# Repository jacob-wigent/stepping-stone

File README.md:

---

> 🚧 Under development

Stepping Stone is a 4-axis stepper motor control platform designed for robotics and CNC development. With hardware built around an STM32G4 MCU and TMC2209 drivers, it supports coordinated multi-axis motion, encoder feedback, stall-sense homing, and CAN/USB connectivity for flexible development and testing. The desktop application connects to the hardware to provide detailed, real-time telemetry and visualization support.

Designed as a “stepping stone” in motion-control prototyping, it bridges the gap between simple stepper driver breakouts and full CNC or robotics systems, providing a reusable platform for early development.

### Navigate

| |  |  |
|-----------|---------|---------|
| **[Hardware](./hardware)** | Circuit design and PCB layout | KiCad design files, simulations |
| **[Firmware](./firmware)** | Microcontroller implementation | STM32 code, CubeMX configuration |
| **[Software](./software)** | Desktop telemetry bridge | GUI application code |

## Planned Features

- **Power Input**: 5-24V input from bench supply or dedicated PSU.
- **Motors**: 4 independent stepper motor channels.
- **Encoders**: 4 quadrature encoder channels.
- **Limits**: 8 limit switch channels and stall-detection support.
- **Safety**: E-Stop system with hardware interlock for motor-enable.
- **Connectivity**: USB 2.0, CAN, I2C, SPI, UART, and GPIO interfaces.
- **Storage**: microSD support and on-board 16MB flash for G-code storage and system logging.
- **User Interface**: Status LEDs, boot/reset buttons, and user-programmable buttons.
- **Telemetry**: Desktop application displaying customizable, real-time telemetry and 3D visualization.

## Roadmap

- [x] System architecture defined
- [x] Component selection finalized
- [x] Schematic capture
- [ ] PCB layout
- [ ] Firmware development
- [ ] Software development

See the [open issues](https://github.com/jacob-wigent/stepping-stone/issues) for a full list of proposed features (and known issues).

## Tools
- **Hardware Design:** KiCad 10.0 for schematic capture and PCB layout
- **Firmware:** STM32CubeIDE or PlatformIO (planned)
- **Software:** [Tauri](https://v2.tauri.app/) user interface/rust bridge for [rerun](https://github.com/rerun-io/rerun) visualization (planned)

## License

This project is released under the **CERN Open Hardware Licence Version 2 – Strongly Reciprocal (CERN-OHL-S v2)**.  

You are free to use, modify, and distribute the hardware and design files, provided that derivative works are also shared under the same license.  

For full license details, see the [LICENSE](LICENSE) file.

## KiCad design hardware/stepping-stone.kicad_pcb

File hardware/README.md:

---

> 🚧 Under development

The Stepping Stone hardware includes an off-the-shelf power supply and a custom PCB designed to provide engineers with a versatile and multi-functional platform capable of driving bipolar stepper motors such as those used in popular 3D printers, desktop CNC machines, and robotics.

## Architecture Overview

- **MCU:** STM32G4
- **Stepper Drivers:** 4x TCM2209

<!-- ## Preliminary Layout

> CREATE DRAW.IO DOCUMENT AND SAVE TO THIS REPOSITORY AS `layout.drawio`

## Power System

- Example

## User Interface

- LEDS!!!!

## Design Considerations

- Route the Gb Ethernet traces under the buck converter.

## Notes

- Hmmm.. -->

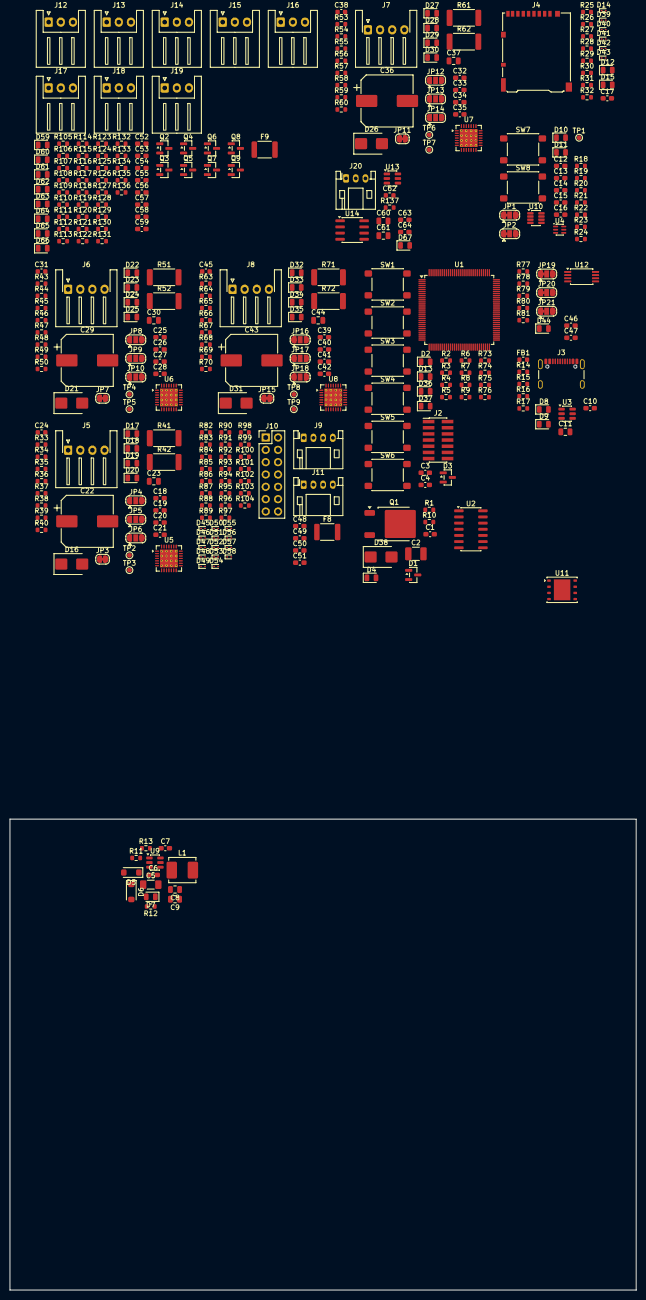
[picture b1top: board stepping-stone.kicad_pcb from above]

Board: 2 copper layers, 129.0 x 97.0 mm, 352 parts (0 on the bottom side), 211 nets, no tracks yet.

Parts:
C1, C3, C6, C7, C10, C12, C13, C14, C15, C16, C17, C18, C19, C20, C21, C25, C26, C27, C28, C32, C33, C34, C35, C39, C40, C41, C42, C46, C47, C48, C49, C50, C51, C52, C53, C54, C55, C56, C57, C58, C59, C63, C64: 0.1uF; C_0603_1608Metric_Pad1.08x0.95mm_HandSolder
C2: 10uF, 50V; C_1210_3225Metric_Pad1.33x2.70mm_HandSolder
C4: 10nF; C_0603_1608Metric_Pad1.08x0.95mm_HandSolder
C5: 4.7uF, 50V; C_1206_3216Metric_Pad1.33x1.80mm_HandSolder
C8, C9, C60, C61: 10uF, 10V; C_0805_2012Metric
C11, C23, C30, C37, C44: 4.7uF, 16V; C_0805_2012Metric
C22, C29, C36, C43: 100uF; CP_Elec_10x10.5
C24, C31, C38, C45: 22nF; C_0603_1608Metric
C62: 1uF; Fuse_0603_1608Metric
D1: 12V; SOT-23
D2, D9, D13, D15, D18, D20, D23, D25, D28, D30, D33, D35, D44, D67: BLUE; D_0805_2012Metric
D3: BAT54S; SOT-23
D4, D19, D24, D29, D34, D37, D59, D60, D61, D62, D63, D64, D65, D66: YELLOW; D_0805_2012Metric
D5, D6: DSS14U; D_SOD-123FL
D7, D8, D11, D12, D17, D22, D27, D32, D36: GREEN; D_0805_2012Metric
D10: RED; D_0805_2012Metric
D14, D45, D48, D50, D57: ESD9B3; D_SOD-923
D16, D21, D26, D31, D38: 28.5V; D_SMB
D39, D40, D41, D42, D43, D46, D47, D49, D51, D52, D53, D54, D55, D56, D58: ESD9B3.3ST5G; D_SOD-923
F8, F9: 500mA, 1A, 150ms; Fuse_1812_4532Metric
FB1: 470@100Mhz; L_0603_1608Metric
J2: STLink Header; PinHeader_2x07_P1.27mm_Vertical_SMD
J3: USB_C_Receptacle_USB2.0_14P; USB_C_Receptacle_GCT_USB4105-xx-A_16P_TopMnt_Horizontal
J4: Micro_SD_Card_Det_Hirose_DM3AT; microSD_HC_Hirose_DM3AT-SF-PEJM5
J5, J6, J7, J8: Conn_01x04; JST_XH_S4B-XH-A-1_1x04_P2.50mm_Horizontal
J9: I2C_A; JST_PH_S4B-PH-K_1x04_P2.00mm_Horizontal
J10: GPIO_Header_Split; PinHeader_2x07_P2.54mm_Vertical
J11: I2C_B; JST_PH_S4B-PH-K_1x04_P2.00mm_Horizontal
J12, J13, J14, J15: LIMIT0; JST_XH_S3B-XH-A_1x03_P2.50mm_Horizontal
J16, J17, J18, J19: LIMIT1; JST_XH_S3B-XH-A_1x03_P2.50mm_Horizontal
J20: CAN; JST_PH_S3B-PH-K_1x03_P2.00mm_Horizontal
JP1: SET1; SolderJumper-3_P1.3mm_Bridged12_RoundedPad1.0x1.5mm
JP2: SET0; SolderJumper-3_P1.3mm_Bridged12_RoundedPad1.0x1.5mm
JP3, JP7, JP11, JP15: VREF; SolderJumper-2_P1.3mm_Bridged_RoundedPad1.0x1.5mm
JP4, JP8, JP12, JP16: MS1/AD0; SolderJumper-3_P1.3mm_Open_RoundedPad1.0x1.5mm
JP5, JP9, JP13, JP17: MS2/AD1; SolderJumper-3_P1.3mm_Open_RoundedPad1.0x1.5mm
JP6, JP10, JP14, JP18: SPREAD; SolderJumper-3_P1.3mm_Open_RoundedPad1.0x1.5mm
JP19: E0; SolderJumper-3_P1.3mm_Bridged12_RoundedPad1.0x1.5mm
JP20: E1; SolderJumper-3_P1.3mm_Bridged12_RoundedPad1.0x1.5mm
JP21: E2; SolderJumper-3_P1.3mm_Bridged12_RoundedPad1.0x1.5mm
L1: 8.2uH; L_Bourns_SRP5030HMT
Q1: DMP4010SK3Q; TO-252-2
Q2, Q3, Q4, Q5, Q6, Q7, Q8, Q9: AO3400A; SOT-23
R1, R2, R3, R5, R6, R8, R9, R10, R19, R20, R22, R25, R26, R27, R28, R29, R31, R33, R36, R37, R38, R43, R46, R47, R48, R53, R56, R57, R58, R63, R66, R67, R68, R77, R78, R84, R89, R90, R91, R92, R101, R102, R103, R104, R105, R108, R111, R114, R121, R124, R127, R130: 10k; R_0603_1608Metric
R4: 18k; R_0603_1608Metric
R7, R14, R80, R81, R82, R83, R107, R110, R113, R116, R123, R126, R129, R132: 2.2k; R_0603_1608Metric
R11: 100k; R_0603_1608Metric
R12, R18, R21, R30, R34, R39, R44, R49, R54, R59, R64, R69, R75, R76, R106, R109, R112, R115, R122, R125, R128, R131: 1k; R_0603_1608Metric
R13: 31.6k; R_0603_1608Metric
R15, R32, R35, R40, R45, R50, R55, R60, R65, R70, R73, R74, R79, R137: 220; R_0603_1608Metric
R16, R17: 5.1k; R_0603_1608Metric
R23, R24, R85, R86, R87, R88, R93, R94, R95, R96, R97, R98, R99, R100, R117, R118, R119, R120, R133, R134, R135, R136: 100R; R_0603_1608Metric
R41, R42, R51, R52, R61, R62, R71, R72: 110m; R_2512_6332Metric
SW1: BOOT; SW_SPST_PTS645Sx43SMTR92
SW2, SW8: RESET; SW_SPST_PTS645Sx43SMTR92
SW3: USER0; SW_SPST_PTS645Sx43SMTR92
SW4: USER2; SW_SPST_PTS645Sx43SMTR92
SW5: USER1; SW_SPST_PTS645Sx43SMTR92
SW6: USER3; SW_SPST_PTS645Sx43SMTR92
SW7: ESTOP; SW_SPST_PTS645Sx43SMTR92
TP1: ~{ESTOP_TRIGGER}; TestPoint_Pad_D1.0mm
TP2, TP4, TP6, TP8: BRA; TestPoint_Pad_D1.0mm
TP3, TP5, TP7, TP9: BRB; TestPoint_Pad_D1.0mm
U1: STM32G474QBT6; LQFP-128_14x14mm_P0.4mm
U2: SN74HC132; SOIC-14_3.9x8.7mm_P1.27mm
U3: USBLC6-2SC6; SOT-23-6
U4: 74LVC1G175; SOT-363_SC-70-6
U5, U6, U7, U8: TMC2209-LA; VQFN-28-1EP_5x5mm_P0.5mm_EP3.7x3.7mm_ThermalVias
U9: LMR51625XDDCR; SOT-23-6
U10: TPS3435; SOT-23-8
U11: W25Q128JVS; WSON-8-1EP_6x5mm_P1.27mm_EP3.4x4.3mm
U12: M24C02-FDW; TSSOP-8_4.4x3mm_P0.65mm
U13: AP3602; SOT-23-6
U14: TJA1051T-3; SOIC-8_3.9x4.9mm_P1.27mm

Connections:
+3.3V: C8.1, C9.1, C12.1, C13.1, C16.1, C17.1, C18.1, C25.1, C32.1, C39.1, C46.1, C47.1, C60.1, C64.1, D3.2 (K), D43.1 (A1), F8.2, F9.2, J2.3 (VCC), J4.4 (VDD), JP1.3 (B), JP2.3 (B), JP4.3 (B), JP5.3 (B), JP6.3 (B), JP8.3 (B), JP9.3 (B), JP10.3 (B), JP12.3 (B), JP13.3 (B), JP14.3 (B), JP16.3 (B), JP17.3 (B), JP18.3 (B), JP19.3 (B), JP20.3 (B), JP21.3 (B), L1.2, R2.1, R5.1, R6.1, R8.1, R9.1, R11.1, R12.1, R18.1, R19.1, R20.1, R25.1, R26.1, R27.1, R28.1, R29.1, R30.1, R31.1, R33.1, R34.1, R35.1, R36.1, R43.1, R44.1, R45.1, R46.1, R53.1, R54.1, R55.1, R56.1, R63.1, R64.1, R65.1, R66.1, R77.1, R78.1, R79.1, R80.2, R81.2, R82.2, R83.2, R84.1, R89.1, R90.1, R91.1, R92.1, R105.1, R106.1, R107.2, R108.1, R109.1, R110.2, R111.1, R112.1, R113.2, R114.1, R115.1, R116.2, R121.1, R122.1, R123.2, R124.1, R125.1, R126.2, R127.1, R128.1, R129.2, R130.1, R131.1, R132.2, SW1.1, U1.6 (VBAT), U1.13 (VDD), U1.31 (VDD), U1.47 (VDD), U1.64 (VDD), U1.79 (VDD), U1.95 (VDD), U1.111 (VDD), U1.128 (VDD), U2.14 (VCC), U4.3 (D), U4.5 (VCC), U5.15 (VCC_IO), U6.15 (VCC_IO), U7.15 (VCC_IO), U8.15 (VCC_IO), U10.2 (~MR), U10.6 (WD-EN), U10.8 (VDD), U11.8 (VCC), U12.8 (VCC), U13.3 (~SHDN), U13.5 (VIN), U14.5 (VIO)
/3.3V Buck Converter/VIN: C5.1, C6.1, D5.1 (K), D6.1 (K), U9.2 (EN), U9.3 (VIN)
/Auxiliary IO/3V3_AUX: D47.1 (A1), D58.1 (A1), F8.1, J9.2, J10.2, J10.4, J11.2
/Auxiliary IO/AIO_A: C48.1, R94.2
/Auxiliary IO/AIO_B: C49.1, R96.2
/Auxiliary IO/AIO_C: C50.1, R98.2
/Auxiliary IO/AIO_D: C51.1, R100.2
/CAN Bus/CAN_5V: C61.1, C63.1, U13.1 (VOUT), U14.3 (VCC)
/CAN Bus/RXD: U14.4 (RXD), U14.8 (S)
/ESTOP/WDI: R22.1, U10.3 (WDI)
/ESTOP/~ESTOP_ACTIVE: D10.1 (K), R21.1, U2.1, U2.4, U2.9, U2.12, U4.4 (Q)
/ESTOP/~ESTOP_RESET: R20.2, R24.2, SW8.1, U4.1 (C)
/ESTOP/~ESTOP_TRIGGER: R19.2, R23.2, SW7.1, TP1.1 (1_1), U4.6 (~CLR), U10.7 (~WDO)
/External Memory/SCL: R80.1, U12.6 (SCL)
/External Memory/SDA: R81.1, U12.5 (SDA)
/External Memory/~CS: R77.2, U11.1 (~CS)
/External Memory/~WC: D44.1 (K), R78.2, U12.7 (~WC)
/Limit Switches/3V3_LIM: F9.1, J12.3, J13.3, J14.3, J15.3, J16.3, J17.3, J18.3, J19.3
/Limit Switches/LIM0: D59.1 (K), Q2.3 (D), R105.2
/Limit Switches/LIM1: D63.1 (K), Q6.3 (D), R121.2
/Limit Switches/LIM2: D60.1 (K), Q3.3 (D), R108.2
/Limit Switches/LIM3: D64.1 (K), Q7.3 (D), R124.2
/Limit Switches/LIM4: D61.1 (K), Q4.3 (D), R111.2
/Limit Switches/LIM5: D65.1 (K), Q8.3 (D), R127.2
/Limit Switches/LIM6: D62.1 (K), Q5.3 (D), R114.2
/Limit Switches/LIM7: D66.1 (K), Q9.3 (D), R130.2
/Microcontroller/BOOT0: R3.1, SW1.2, U1.123 (PB8)
/Microcontroller/DRV0_DIR: D18.1 (K), R40.1, U5.19 (DIR)
/Microcontroller/DRV0_STEP: R38.1, U5.16 (STEP)
/Microcontroller/DRV1_DIR: D23.1 (K), R50.1, U6.19 (DIR)
/Microcontroller/DRV1_STEP: R48.1, U6.16 (STEP)
/Microcontroller/DRV2_DIR: D28.1 (K), R60.1, U7.19 (DIR)
/Microcontroller/DRV2_STEP: R58.1, U7.16 (STEP)
/Microcontroller/DRV3_DIR: D33.1 (K), R70.1, U8.19 (DIR)
/Microcontroller/DRV3_STEP: R68.1, U8.16 (STEP)
/Microcontroller/NRST: C3.1, J2.12 (~RST), R2.2, SW2.1, U1.21 (PG10)
/Microcontroller/SD_CLK: D40.1 (A1), J4.5 (CLK)
/Microcontroller/SD_CS: D42.1 (A1), J4.2 (DAT3/CD), R28.2
/Microcontroller/SD_PICO: D41.1 (A1), J4.3 (CMD), R27.2
/Microcontroller/SD_POCI: D39.1 (A1), J4.7 (DAT0), R26.2
/Microcontroller/SD_~DET: D12.1 (K), D14.1 (A1), J4.9 (DET_B), R31.2
/Microcontroller/SWCLK: J2.6 (JCLK/SWCLK), U1.98 (PA14)
/Microcontroller/SWDIO: J2.4 (JTMS/SWDIO), U1.96 (PA13)
/Microcontroller/SWO: J2.8 (JTDO/SWO), U1.118 (PB3)
/Microcontroller/USB_DM: U1.92 (PA11), U3.6 (I/O1)
/Microcontroller/USB_DP: U1.93 (PA12), U3.4 (I/O2)
/Microcontroller/USER_BTN_0: R5.2, SW3.1
/Microcontroller/USER_BTN_1: R8.2, SW5.1
/Microcontroller/USER_BTN_2: R6.2, SW4.1
/Microcontroller/USER_BTN_3: R9.2, SW6.1
/Microcontroller/VMOTOR_SENSE: C4.1, D3.3 (COM), R4.2, R7.1
/Stepper Driver 0/1A: J5.1, U5.24 (OA1)
/Stepper Driver 0/1B: J5.2, U5.26 (OB1)
/Stepper Driver 0/2A: J5.3, U5.21 (OA2)
/Stepper Driver 0/2B: J5.4, U5.1 (OB2)
/Stepper Driver 0/DIAG: R39.1, U5.11 (DIAG)
/Stepper Driver 0/MS1/AD0: JP4.2 (C), U5.9 (MS1/AD0)
/Stepper Driver 0/MS1/AD1: JP5.2 (C), U5.10 (MS2/AD1)
/Stepper Driver 0/SPREAD: JP6.2 (C), U5.7 (SPREAD)
/Stepper Driver 0/TMC_5V: C23.1, U5.8 (5VOUT)
/Stepper Driver 0/~EN: D17.1 (K), R33.2, U2.3, U5.2 (~EN)
/Stepper Driver 1/1A: J6.1, U6.24 (OA1)
/Stepper Driver 1/1B: J6.2, U6.26 (OB1)
/Stepper Driver 1/2A: J6.3, U6.21 (OA2)
/Stepper Driver 1/2B: J6.4, U6.1 (OB2)
/Stepper Driver 1/DIAG: R49.1, U6.11 (DIAG)
/Stepper Driver 1/MS1/AD0: JP8.2 (C), U6.9 (MS1/AD0)
/Stepper Driver 1/MS1/AD1: JP9.2 (C), U6.10 (MS2/AD1)
/Stepper Driver 1/SPREAD: JP10.2 (C), U6.7 (SPREAD)
/Stepper Driver 1/TMC_5V: C30.1, U6.8 (5VOUT)
/Stepper Driver 1/~EN: D22.1 (K), R43.2, U2.6, U6.2 (~EN)
/Stepper Driver 2/1A: J7.1, U7.24 (OA1)
/Stepper Driver 2/1B: J7.2, U7.26 (OB1)
/Stepper Driver 2/2A: J7.3, U7.21 (OA2)
/Stepper Driver 2/2B: J7.4, U7.1 (OB2)
/Stepper Driver 2/DIAG: R59.1, U7.11 (DIAG)
/Stepper Driver 2/MS1/AD0: JP12.2 (C), U7.9 (MS1/AD0)
/Stepper Driver 2/MS1/AD1: JP13.2 (C), U7.10 (MS2/AD1)
/Stepper Driver 2/SPREAD: JP14.2 (C), U7.7 (SPREAD)
/Stepper Driver 2/TMC_5V: C37.1, U7.8 (5VOUT)
/Stepper Driver 2/~EN: D27.1 (K), R53.2, U2.8, U7.2 (~EN)
/Stepper Driver 3/1A: J8.1, U8.24 (OA1)
/Stepper Driver 3/1B: J8.2, U8.26 (OB1)
/Stepper Driver 3/2A: J8.3, U8.21 (OA2)
/Stepper Driver 3/2B: J8.4, U8.1 (OB2)
/Stepper Driver 3/DIAG: R69.1, U8.11 (DIAG)
/Stepper Driver 3/MS1/AD0: JP16.2 (C), U8.9 (MS1/AD0)
/Stepper Driver 3/MS1/AD1: JP17.2 (C), U8.10 (MS2/AD1)
/Stepper Driver 3/SPREAD: JP18.2 (C), U8.7 (SPREAD)
/Stepper Driver 3/TMC_5V: C44.1, U8.8 (5VOUT)
/Stepper Driver 3/~EN: D32.1 (K), R63.2, U2.11, U8.2 (~EN)
Earth: J3.SH (SHIELD), J4.SH (SHIELD)
GND: C1.2, C2.2, C3.2, C4.2, C5.2, C6.2, C8.2, C9.2, C10.2, C11.2, C12.2, C13.2, C14.2, C15.2, C16.2, C17.2, C18.2, C20.2, C21.2, C22.2, C23.2, C25.2, C27.2, C28.2, C29.2, C30.2, C32.2, C34.2, C35.2, C36.2, C37.2, C39.2, C41.2, C42.2, C43.2, C44.2, C46.2, C47.2, C48.2, C49.2, C50.2, C51.2, C52.2, C53.2, C54.2, C55.2, C56.2, C57.2, C58.2, C59.2, C60.2, C61.2, C63.2, C64.2, D2.1 (K), D3.1 (A), D4.1 (K), D7.1 (K), D8.1 (K), D9.1 (K), D11.1 (K), D13.1 (K), D14.2 (A2), D15.1 (K), D16.1 (A1), D19.1 (K), D20.1 (K), D21.1 (A1), D24.1 (K), D25.1 (K), D26.1 (A1), D29.1 (K), D30.1 (K), D31.1 (A1), D34.1 (K), D35.1 (K), D36.1 (K), D37.1 (K), D38.1 (A1), D39.2 (A2), D40.2 (A2), D41.2 (A2), D42.2 (A2), D43.2 (A2), D45.2 (A2), D46.2 (A2), D47.2 (A2), D48.2 (A2), D49.2 (A2), D50.2 (A2), D51.2 (A2), D52.2 (A2), D53.2 (A2), D54.2 (A2), D55.2 (A2), D56.2 (A2), D57.2 (A2), D58.2 (A2), D67.1 (K), J2.5 (GND), J2.7 (GND), J2.11 (GNDDetect), J3.A1 (GND), J3.A12 (GND), J3.B1 (GND), J3.B12 (GND), J4.6 (VSS), J4.10 (DET_A), J9.1, J10.1, J10.3, J11.1, J12.2, J13.2, J14.2, J15.2, J16.2, J17.2, J18.2, J19.2, J20.1, JP1.1 (A), JP2.1 (A), JP4.1 (A), JP5.1 (A), JP6.1 (A), JP8.1 (A), JP9.1 (A), JP10.1 (A), JP12.1 (A), JP13.1 (A), JP14.1 (A), JP16.1 (A), JP17.1 (A), JP18.1 (A), JP19.1 (A), JP20.1 (A), JP21.1 (A), Q2.2 (S), Q3.2 (S), Q4.2 (S), Q5.2 (S), Q6.2 (S), Q7.2 (S), Q8.2 (S), Q9.2 (S), R1.2, R3.2, R7.2, R13.2, R16.2, R17.2, R22.2, R37.2, R38.2, R41.1, R42.1, R47.2, R48.2, R51.1, R52.1, R57.2, R58.2, R61.1, R62.1, R67.2, R68.2, R71.1, R72.1, R101.2, R102.2, R103.2, R104.2, SW2.2, SW3.2, SW4.2, SW5.2, SW6.2, SW7.2, SW8.2, U1.12 (VSS), U1.30 (VSS), U1.42 (VSSA), U1.46 (VSS), U1.63 (VSS), U1.78 (VSS), U1.94 (VSS), U1.110 (VSS), U1.127 (VSS), U2.7 (GND), U3.2 (GND), U4.2 (GND), U5.3 (GND), U5.13 (CLK), U5.18 (GND), U5.20 (STDBY), U5.25 (NC), U5.29 (GND), U6.3 (GND), U6.13 (CLK), U6.18 (GND), U6.20 (STDBY), U6.25 (NC), U6.29 (GND), U7.3 (GND), U7.13 (CLK), U7.18 (GND), U7.20 (STDBY), U7.25 (NC), U7.29 (GND), U8.3 (GND), U8.13 (CLK), U8.18 (GND), U8.20 (STDBY), U8.25 (NC), U8.29 (GND), U9.4 (GND), U10.4 (GND), U11.4 (GND), U12.4 (VSS), U13.2 (GND), U14.2 (GND)
unnamed: C14.1, R23.1
unnamed: C15.1, R24.1
unnamed: C52.1, R117.1
unnamed: C53.1, R118.1
unnamed: C54.1, R119.1
unnamed: C55.1, R120.1
unnamed: C56.1, R133.1
unnamed: C57.1, R134.1
unnamed: C58.1, R135.1
unnamed: C59.1, R136.1
unnamed: D1.1 (A), Q1.1 (G), R1.1
unnamed: D2.2 (A), R73.2
unnamed: D4.2 (A), R10.2
unnamed: D7.2 (A), R12.2
unnamed: D8.2 (A), R14.2
unnamed: D9.2 (A), R15.2
unnamed: D10.2 (A), R18.2
unnamed: D11.2 (A), R21.2
unnamed: D12.2 (A), R30.2
unnamed: D13.2 (A), R74.2
unnamed: D15.2 (A), R32.2
unnamed: D17.2 (A), R34.2
unnamed: D18.2 (A), R35.2
unnamed: D19.2 (A), R39.2
unnamed: D20.2 (A), R40.2
unnamed: D22.2 (A), R44.2
unnamed: D23.2 (A), R45.2
unnamed: D24.2 (A), R49.2
unnamed: D25.2 (A), R50.2
unnamed: D27.2 (A), R54.2
unnamed: D28.2 (A), R55.2
unnamed: D29.2 (A), R59.2
unnamed: D30.2 (A), R60.2
unnamed: D32.2 (A), R64.2
unnamed: D33.2 (A), R65.2
unnamed: D34.2 (A), R69.2
unnamed: D35.2 (A), R70.2
unnamed: D36.2 (A), R75.2
unnamed: D37.2 (A), R76.2
unnamed: D44.2 (A), R79.2
unnamed: D45.1 (A1), J9.3, J11.3, R82.1, R88.2
unnamed: D46.1 (A1), J9.4, J11.4, R83.1, R86.2
unnamed: D48.1 (A1), J10.14, R87.2
unnamed: D49.1 (A1), J10.13, R84.2, R85.2
unnamed: D50.1 (A1), J10.5, R89.2, R99.2, R101.1
unnamed: D51.1 (A1), J10.7, R90.2, R97.2, R102.1
unnamed: D52.1 (A1), J10.9, R91.2, R95.2, R103.1
unnamed: D53.1 (A1), J10.11, R92.2, R93.2, R104.1
unnamed: D54.1 (A1), J10.12, R94.1
unnamed: D55.1 (A1), J10.10, R96.1
unnamed: D56.1 (A1), J10.8, R98.1
unnamed: D57.1 (A1), J10.6, R100.1
unnamed: D59.2 (A), R106.2
unnamed: D60.2 (A), R109.2
unnamed: D61.2 (A), R112.2
unnamed: D62.2 (A), R115.2
unnamed: D63.2 (A), R122.2
unnamed: D64.2 (A), R125.2
unnamed: D65.2 (A), R128.2
unnamed: D66.2 (A), R131.2
unnamed: D67.2 (A), R137.2
unnamed: J3.A5 (CC1), R17.1
unnamed: J3.B5 (CC2), R16.1
unnamed: J3.A6 (D+), J3.B6 (D+), U3.3 (I/O2)
unnamed: J3.A7 (D-), J3.B7 (D-), U3.1 (I/O1)
unnamed: J4.8 (DAT1), R25.2
unnamed: J4.1 (DAT2), R29.2
unnamed: J12.1, Q2.1 (G), R107.1, R117.2
unnamed: J13.1, Q3.1 (G), R110.1, R118.2
unnamed: J14.1, Q4.1 (G), R113.1, R119.2
unnamed: J15.1, Q5.1 (G), R116.1, R120.2
unnamed: J16.1, Q6.1 (G), R123.1, R133.2
unnamed: J17.1, Q7.1 (G), R126.1, R134.2
unnamed: J18.1, Q8.1 (G), R129.1, R135.2
unnamed: J19.1, Q9.1 (G), R132.1, R136.2
unnamed: J20.2, U14.7 (CANH)
unnamed: J20.3, U14.6 (CANL)
unnamed: JP1.2 (C), U10.5 (SET1)
unnamed: JP2.2 (C), U10.1 (SET0)
unnamed: JP3.1 (A), U5.17 (VREF)
unnamed: JP3.2 (B), R36.2, R37.1
unnamed: JP7.1 (A), U6.17 (VREF)
unnamed: JP7.2 (B), R46.2, R47.1
unnamed: JP11.1 (A), U7.17 (VREF)
unnamed: JP11.2 (B), R56.2, R57.1
unnamed: JP15.1 (A), U8.17 (VREF)
unnamed: JP15.2 (B), R66.2, R67.1
unnamed: JP19.2 (C), U12.1 (E0)
unnamed: JP20.2 (C), U12.2 (E1)
unnamed: JP21.2 (C), U12.3 (E2)
unnamed: C10.1, FB1.1, J3.A4 (VBUS), J3.A9 (VBUS), J3.B4 (VBUS), J3.B9 (VBUS), U3.5 (VBUS)
unnamed: R42.2, TP2.1 (1_1), U5.23 (BRA)
unnamed: R41.2, TP3.1 (1_1), U5.27 (BRB)
unnamed: C24.2, U5.5 (CPI)
unnamed: C24.1, U5.4 (CPO)
unnamed: C19.2, U5.6 (VCP)
unnamed: R52.2, TP4.1 (1_1), U6.23 (BRA)
unnamed: R51.2, TP5.1 (1_1), U6.27 (BRB)
unnamed: C31.2, U6.5 (CPI)
unnamed: C31.1, U6.4 (CPO)
unnamed: C26.2, U6.6 (VCP)
unnamed: R62.2, TP6.1 (1_1), U7.23 (BRA)
unnamed: R61.2, TP7.1 (1_1), U7.27 (BRB)
unnamed: C38.2, U7.5 (CPI)
unnamed: C38.1, U7.4 (CPO)
unnamed: C33.2, U7.6 (VCP)
unnamed: R72.2, TP8.1 (1_1), U8.23 (BRA)
unnamed: R71.2, TP9.1 (1_1), U8.27 (BRB)
unnamed: C45.2, U8.5 (CPI)
unnamed: C45.1, U8.4 (CPO)
unnamed: C40.2, U8.6 (VCP)
unnamed: C7.1, U9.6 (CB)
unnamed: R11.2, R13.1, U9.1 (FB)
unnamed: C7.2, L1.1, U9.5 (SW)
unnamed: C62.1, U13.6 (C+)
unnamed: C62.2, U13.4 (C-)
VBUS: C11.1, D6.2 (A), FB1.2, R14.1
VMOTOR: C1.1, C2.1, C19.1, C20.1, C21.1, C22.1, C26.1, C27.1, C28.1, C29.1, C33.1, C34.1, C35.1, C36.1, C40.1, C41.1, C42.1, C43.1, D1.3 (K), D5.2 (A), D16.2 (A2), D21.2 (A2), D26.2 (A2), D31.2 (A2), D38.2 (A2), Q1.3 (S), R4.1, R10.1, U5.22 (VS), U5.28 (VS), U6.22 (VS), U6.28 (VS), U7.22 (VS), U7.28 (VS), U8.22 (VS), U8.28 (VS)

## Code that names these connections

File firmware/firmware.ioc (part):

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Mcu.Name=STM32G474Q(B-C-E)Tx
Mcu.Package=LQFP128
Mcu.UserName=STM32G474QBTx
PA11.Mode=Device
PA11.Signal=USB_DM
PA12.Mode=Device
PA12.Signal=USB_DP
PA13.Mode=Trace_Asynchronous_SW
PA13.Signal=SYS_JTMS-SWDIO
PA14.Mode=Trace_Asynchronous_SW
PA14.Signal=SYS_JTCK-SWCLK
PA8.GPIOParameters=GPIO_Label
PA8.GPIO_Label=VMOTOR_SENSE
PA8.Mode=IN1-Single-Ended
PA8.Signal=ADC5_IN1
PB3.Mode=Trace_Asynchronous_SW
PB3.Signal=SYS_JTDO-SWO
PF0-OSC_IN.Mode=HSE-External-Oscillator
PF0-OSC_IN.Signal=RCC_OSC_IN
PF1-OSC_OUT.Mode=HSE-External-Oscillator
PF1-OSC_OUT.Signal=RCC_OSC_OUT
RCC.HSE_VALUE=24000000
RCC.SYSCLKFreq_VALUE=160000000
RCC.SYSCLKSource=RCC_SYSCLKSOURCE_PLLCLK
board=custom

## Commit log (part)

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2026-06-13 Initial plan
2026-06-13 Update README target capabilities feature list
2026-06-13 Create KiCad project
    Created KiCad 10.0 project, schematic, and pcb files.
2026-06-13 Added diagram.drawio
2026-06-13 Added diagram.png
2026-06-13 Add logo and update base README
2026-06-13 Update README with detailed software tool info
    Updated software tool description to include rerun bridge.
2026-06-13 Update KiCad drawing sheets
2026-06-14 Update roadmap
2026-06-14 Configure CubeMX for USB PD
2026-06-14 Add MCU and USB symbols
2026-06-15 Draft power inputs sheet
    Added USB C PD input and external supply, with ideal diode ORing.
2026-06-21 Finalize source select
2026-06-21 Add 3.3V buck converter
2026-06-22 Create MCU schematic
